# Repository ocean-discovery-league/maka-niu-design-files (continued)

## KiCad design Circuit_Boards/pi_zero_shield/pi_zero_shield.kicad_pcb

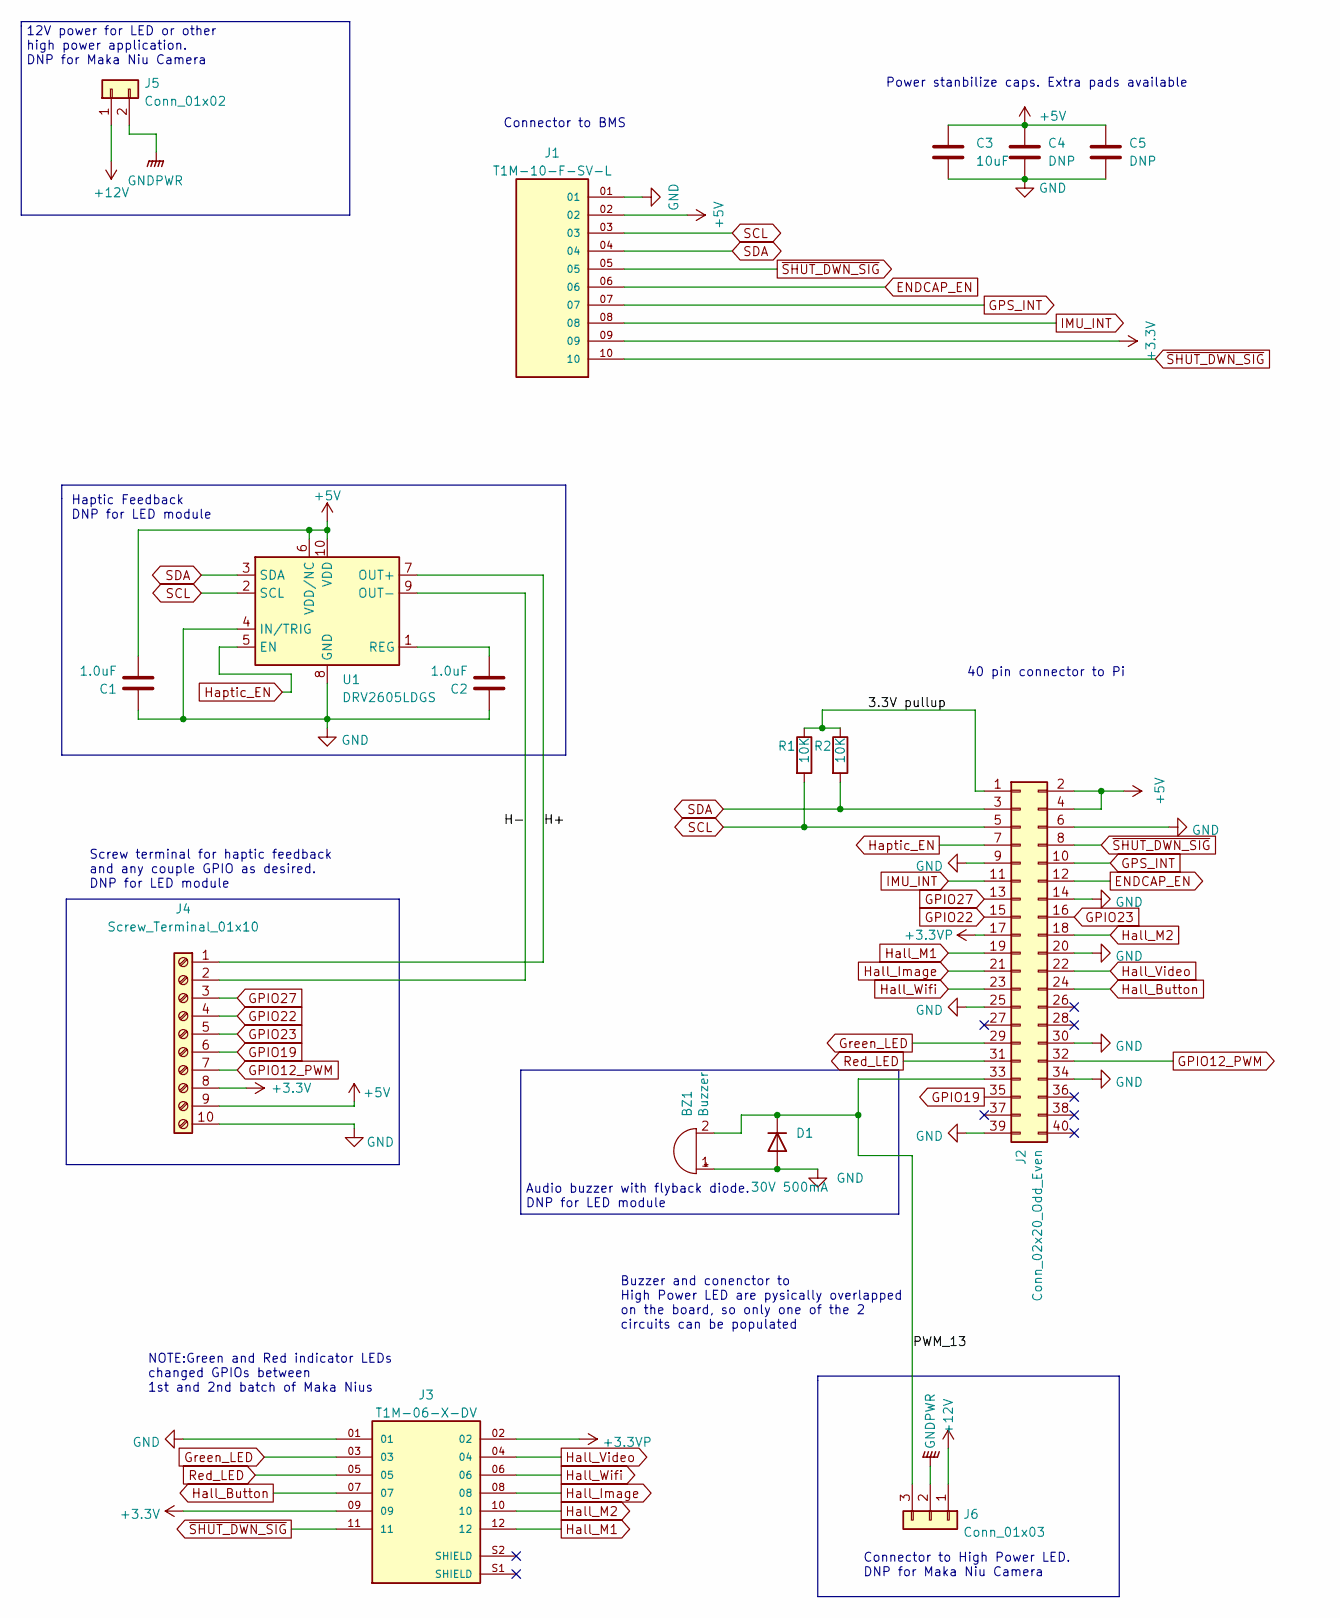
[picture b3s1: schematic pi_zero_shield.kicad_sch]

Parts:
BZ1: Buzzer; Buzzer_12x9.5RM7.6; LCSC C968749
C1, C2: 1.0uF; C_0603_1608Metric; LCSC C90540
C3: 10uF; C_1206_3216Metric_Pad1.33x1.80mm_HandSolder; DigiKey 587-TMK316AB7106ML-TCT-ND
C4, C5: DNP; C_1206_3216Metric_Pad1.33x1.80mm_HandSolder
D1: 30V 500mA; D_SOD-123; DigiKey MBR0530T1GOSCT-ND
J1: T1M-10-F-SV-L; SAMTEC_T1M-10-F-SV-L; Digikey SAM16035-ND
J2: Conn_02x20_Odd_Even; Pi_PinSocket_2x20; Digikey 952-3218-ND
J3: T1M-06-X-DV; SAMTEC_T1M-06-X-DV; Digikey -Get from Samtec
J4: Screw_Terminal_01x10; PinHeader_1x10_P2.54mm_Vertical; Digikey ED10567-ND
J5: Conn_01x02; Molex_Micro-Fit_3.0_43650-0210_1x02-1MP_P3.00mm_Horizontal; Digikey WM6264CT-ND
J6: Conn_01x03; Molex_Micro-Fit_3.0_43650-0310_1x03-1MP_P3.00mm_Horizontal; Digikey WM1886CT-ND
R1, R2: 10K; R_0603_1608Metric; LCSC C25804
U1: DRV2605LDGS; VSSOP-10_3x3mm_P0.5mm; LCSC C527464

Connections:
+3.3VP: J2.17, J3.02
+3V3: J1.09, J3.09, J4.8
+5V: C1.1, C3.1, C4.1, C5.1, J1.02, J2.2, J2.4, J4.9, U1.6 (VDD/NC), U1.10 (VDD)
+12V: J5.1, J6.1
/3.3V pullup: J2.1, R1.1, R2.1
/H+: J4.1, U1.7 (OUT+)
/H-: J4.2, U1.9 (OUT-)
/PWM_13: BZ1.2 (+), D1.1 (K), J2.33, J6.3
ENDCAP_EN: J1.06, J2.12
GND: BZ1.1 (-), C1.2, C2.2, C3.2, C4.2, C5.2, D1.2 (A), J1.01, J2.6, J2.9, J2.14, J2.20, J2.25, J2.30, J2.34, J2.39, J3.01, J4.10, U1.4 (IN/TRIG), U1.8 (GND)
GNDPWR: J5.2, J6.2
GPIO12_PWM: J2.32, J4.7
GPIO19: J2.35, J4.6
GPIO22: J2.15, J4.4
GPIO23: J2.16, J4.5
GPIO27: J2.13, J4.3
GPS_INT: J1.07, J2.10
Green_LED: J2.29, J3.03
Hall_Button: J2.24, J3.07
Hall_Image: J2.21, J3.08
Hall_M1: J2.19, J3.12
Hall_M2: J2.18, J3.10
Hall_Video: J2.22, J3.04
Hall_Wifi: J2.23, J3.06
Haptic_EN: J2.7, U1.5 (EN)
IMU_INT: J1.08, J2.11
unnamed: C2.1, U1.1 (REG)
Red_LED: J2.31, J3.05
SCL: J1.03, J2.5, R1.2, U1.2 (SCL)
SDA: J1.04, J2.3, R2.2, U1.3 (SDA)
~SHUT_DWN_SIG: J1.05, J1.10, J2.8, J3.11

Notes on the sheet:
Connector to High Power LED. DNP for Maka Niu Camera
Connector to BMS
Buzzer and conenctor to High Power LED are pysically overlapped on the board, so only one of the 2 circuits can be populated
NOTE:Green and Red indicator LEDs changed GPIOs between 1st and 2nd batch of Maka Nius
12V power for LED or other high power application. DNP for Maka Niu Camera
Haptic Feedback DNP for LED module
Power stanbilize caps. Extra pads available
Screw terminal for haptic feedback and any couple GPIO as desired. DNP for LED module
40 pin connector to Pi
Audio buzzer with flyback diode. DNP for LED module

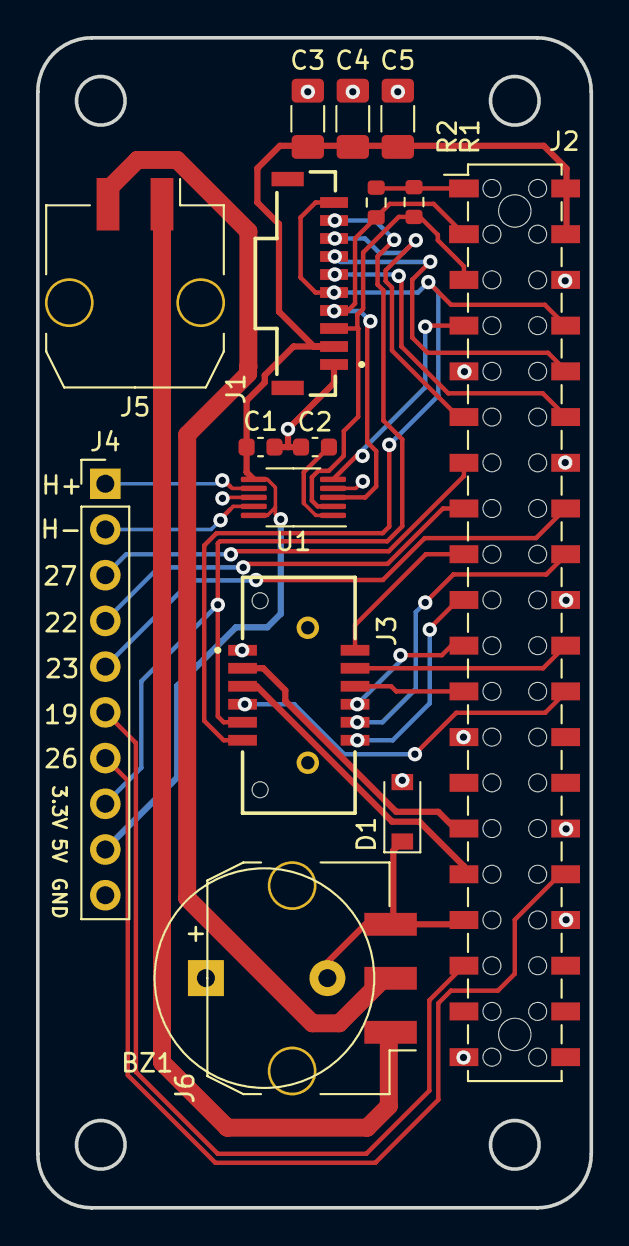
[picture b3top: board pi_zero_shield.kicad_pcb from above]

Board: 2 copper layers, 30.8 x 65.0 mm, 16 parts (0 on the bottom side), 31 nets.

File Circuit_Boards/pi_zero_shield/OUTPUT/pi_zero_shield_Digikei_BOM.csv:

Reference, Quantity, Value, Buy Digikey, Digikey, LCSC, Mouser
BZ1 ,1,Buzzer,skip,668-1466-ND,C968749,
C1 C2 ,2,1.0uF,skip,1276-1102-1-ND,C90540,
J1 ,1,T1M-10-F-SV-L,skip: SAMTEC,SAM16035-ND,,
J2 ,1,Conn_02x20_Odd_Even,Buy,952-3218-ND,,
J3 ,1,T1M-06-X-DV,skip: SAMTEC,,,
J4 ,1,Screw_Terminal_01x10,Buy,ED10567-ND,,
J5 ,1,Conn_01x02,Buy,WM6264CT-ND,,
J6 ,1,Conn_01x03,Buy,WM1886CT-ND,,
R1 R2 ,2,10K,skip,RNCP0603FTD10K0CT-ND,C25804,
U1 ,1,DRV2605LDGS,Buy: Mouser,296-40032-1-ND,C527464,595-DRV2605LDGSR
Motor,1,,Buy,1670-VC1234B016F-ND,,

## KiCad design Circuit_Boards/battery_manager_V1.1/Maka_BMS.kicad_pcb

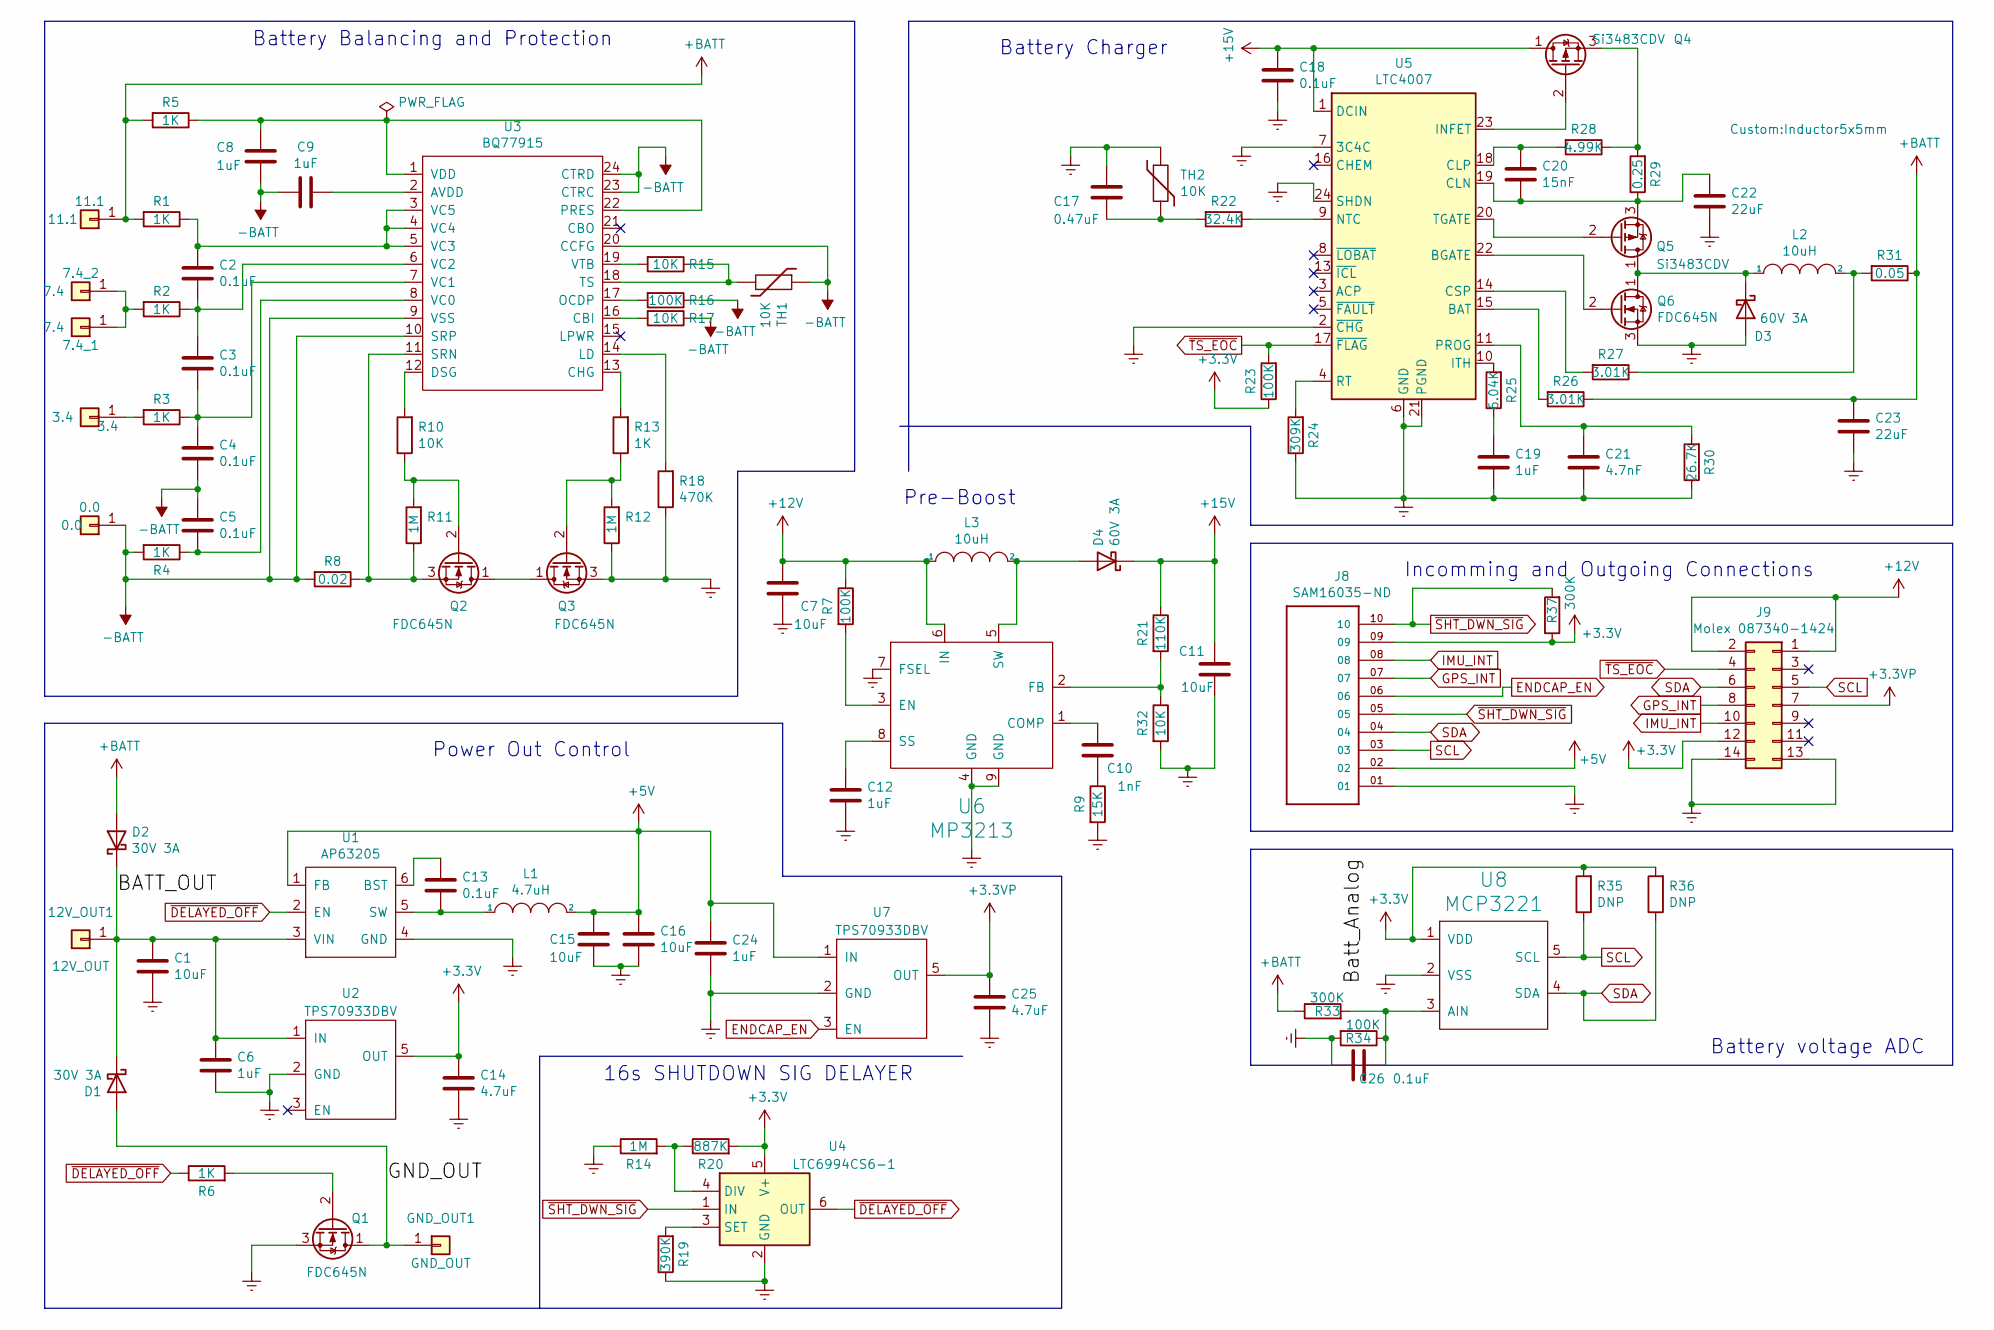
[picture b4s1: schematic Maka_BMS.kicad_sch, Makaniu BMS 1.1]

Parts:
0.0: 0.0; TruHole_Batter_Contact_Pad_with_9mm_clear; Digikey 36-240-ND
3.4: 3.4; TestPoint_THTPad_D1.5mm_Drill0.7mm
7.4_1, 7.4_2: 7.4; TruHole_Batter_Contact_Pad_with_9mm_clear; Digikey 36-240-ND
11.1: 11.1; TestPoint_THTPad_D1.5mm_Drill0.7mm
12V_OUT1: 12V_OUT; TestPoint_THTPad_D1.5mm_Drill0.7mm
C1, C7, C11, C15, C16: 10uF; C_0603_1608Metric; Digikey 490-7202-1-ND
C2, C3, C4, C5, C13, C18, C26: 0.1uF; C_0402_1005Metric; Digikey 732-7495-1-ND
C6, C8, C9, C12, C19, C24: 1uF; C_0402_1005Metric; Digikey 490-10017-1-ND
C10: 1nF; C_0402_1005Metric; Digikey 478-1101-2-ND
C14, C25: 4.7uF; C_0603_1608Metric; Digikey 1276-1900-1-ND
C17: 0.47uF; C_0402_1005Metric; Digikey 490-12269-1-ND
C20: 15nF; C_0402_1005Metric; Digikey 311-1713-1-ND
C21: 4.7nF; C_0402_1005Metric; Digikey 311-1039-1-ND
C22, C23: 22uF; C_0603_1608Metric; Digikey 1276-7076-1-ND
D1, D2: 30V 3A; SMA(DO-214AC); Digikey B340A-FDICT-ND
D3, D4: 60V 3A; D_SOD-123EP; Digikey SSA36CT-ND
GND_OUT1: GND_OUT; TestPoint_THTPad_D1.5mm_Drill0.7mm
J8: ‎SAM16035-ND‎; SAMTEC_T1M-10-F-SH-L-K; Digikey SAM11993-ND
J9: Molex 087340-1424; Molex_87340-1424_B; Digikey 23-0873401424-ND
L1: 4.7uH; L_1008_2520Metric; Digikey 490-10651-1-ND
L2, L3: 10uH; Inductor5x5mm; Digikey 1589-MPL-SE6040-100CT-ND
Q1, Q2, Q3, Q6: FDC645N; SOT-23-6_mosfet; Digikey FDC655BNCT-ND
Q4, Q5: Si3483CDV; SOT-23-6_mosfet; Digikey CPH6350-TL-WOSCT-ND
R1, R2, R3, R4, R5, R6, R13: 1K; R_0402_1005Metric; Digikey YAG1234CT-ND
R7, R16, R23, R34: 100K; R_0402_1005Metric; Digikey 311-100KLRCT-ND
R8: 0.02; R_1206_3216Metric; Digikey WSLP-.02CT-ND
R9: 15K; R_0402_1005Metric; Digikey 311-15.0KLRTR-ND
R10, R15, R17, R32: 10K; R_0402_1005Metric; Digikey 311-10.0KLRCT-ND
R11, R12, R14: 1M; R_0402_1005Metric; Digikey 311-1.00MLRCT-ND
R18: 470K; R_0402_1005Metric; Digikey 311-470KJRCT-ND
R19: 390K; R_0402_1005Metric; Digikey YAG3143CT-ND
R20: 887K; R_0402_1005Metric; Digikey YAG5696CT-ND
R21: 110K; R_0402_1005Metric; Digikey 311-110KLRCT-ND
R22: 32.4K; R_0402_1005Metric; Digikey YAG3119CT-ND
R24: 309K; R_0402_1005Metric; Digikey YAG3108CT-ND
R25: 6.04K; R_0402_1005Metric; Digikey YAG2293CT-ND
R26, R27: 3.01K; R_0402_1005Metric; Digikey 311-3.01KLRCT-ND
R28: 4.99K; R_0402_1005Metric; Digikey YAG1447CT-ND
R29: 0.25; R_1206_3216Metric; Digikey 311-0.25ANCT-ND
R30: 26.7K; R_0402_1005Metric; Digikey YAG3081CT-ND
R31: 0.05; R_1206_3216Metric; Digikey MCS1632R050FERCT-ND
R33, R37: 300K; R_0402_1005Metric; Digikey 311-300KLRCT-ND
R35, R36: DNP; R_0402_1005Metric
TH1: 10K; R_0402_1005Metric; Digikey 495-5814-1-ND
TH2: 10K; R_0402_1005Metric; Digikey 311-10.0KLRCT-ND
U1: AP63205; TSOT-23-6; Digikey AP63205WU-7DICT-ND
U2, U7: TPS70933DBV; SOT-23-5; Digikey 497-6979-1-ND
U3: BQ77915; TSSOP-24_4.4x7.8mm_P0.65mm; Digikey 296-50995-1-ND
U4: LTC6994CS6-1; TSOT-23-6; Digikey LTC6994CS6-1#TRMPBFCT-ND
U5: LTC4007; SSOP-24_3.9x8.7mm_P0.635mm; Digikey LTC4007EGN#PBF-ND
U6: MP3213; MSOP-8-1EP_3x3mm_P0.65mm_EP1.95x2.15mm; Digikey 1589-1626-1-ND
U8: MCP3221; SOT-23-5; LCSC C36310

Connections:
+3.3VP: C25.2, J9.7, U7.5 (OUT)
+3V3: C14.2, J8.09, J9.12, R20.2, R23.1, R35.2, R36.2, R37.1, U2.5 (OUT), U4.5 (V+), U8.1 (VDD)
+5V: C15.2, C16.2, C24.2, J8.02, L1.2, U1.1 (FB), U7.1 (IN)
+12V: C7.1, J9.1, J9.2, L3.1, R7.1, U6.6 (IN)
+15V: C11.1, C18.2, D4.1 (K), Q4.1 (D), R21.1, U5.1 (DCIN)
+BATT: 11.1.1, C23.2, D2.2 (A), R1.2, R5.2, R26.1, R31.1, R33.1
-BATT: 0.0.1, C4.1, C5.2, C8.1, C9.2, R4.2, R8.2, R16.1, R17.1, TH1.1, U3.9 (VSS), U3.10 (SRP), U3.20 (CCFG), U3.23 (CTRC), U3.24 (CTRD)
/BATT_OUT: 12V_OUT1.1, C1.2, C6.2, D1.1 (K), D2.1 (K), U1.3 (VIN), U2.1 (IN)
/GND_OUT: D1.2 (A), GND_OUT1.1, Q1.1 (D)
ENDCAP_EN: J8.06, U7.3 (EN)
Earth: C1.1, C6.1, C7.2, C11.2, C12.1, C14.1, C15.1, C16.1, C17.2, C18.1, C19.1, C21.1, C22.1, C23.1, C24.1, C25.1, C26.2, D3.2 (A), J8.01, J9.13, J9.14, Q1.3 (S), Q3.3 (S), Q6.3 (S), R9.2, R12.1, R14.1, R18.1, R19.1, R24.1, R30.1, R32.2, R34.2, TH2.1, U1.4 (GND), U2.2 (GND), U4.2 (GND), U5.2 (~CHG), U5.6 (GND), U5.7 (3C4C), U5.21 (PGND), U5.24 (SHDN), U6.4 (GND), U6.7 (FSEL), U6.9 (GND), U7.2 (GND), U8.2 (VSS)
GPS_INT: J8.07, J9.8
IMU_INT: J8.08, J9.10
unnamed: 3.4.1, R3.2
unnamed: 7.4_1.1, 7.4_2.1, R2.2
unnamed: C2.1, C3.2, R2.1, U3.6 (VC2)
unnamed: C2.2, R1.1, U3.3 (VC5), U3.4 (VC4), U3.5 (VC3)
unnamed: C3.1, C4.2, R3.1, U3.7 (VC1)
unnamed: C5.1, R4.1, U3.8 (VC0)
unnamed: C8.2, R5.1, U3.1 (VDD), U3.22 (PRES)
unnamed: C9.1, U3.2 (AVDD)
unnamed: C10.1, U6.1 (COMP)
unnamed: C10.2, R9.1
unnamed: C12.2, U6.8 (SS)
unnamed: C13.1, L1.1, U1.5 (SW)
unnamed: C13.2, U1.6 (BST)
unnamed: C17.1, R22.2, TH2.2
unnamed: C19.2, R25.1
unnamed: C20.1, C22.2, Q5.3 (S), R29.1, U5.19 (CLN)
unnamed: C20.2, R28.2, U5.18 (CLP)
unnamed: C21.2, R30.2, U5.11 (PROG)
unnamed: D3.1 (K), L2.1, Q5.1 (D), Q6.1 (D)
unnamed: D4.2 (A), L3.2, U6.5 (SW)
unnamed: L2.2, R27.1, R31.2
unnamed: Q1.2 (G), R6.2
unnamed: Q2.1 (D), Q3.1 (D)
unnamed: Q2.2 (G), R10.1, R11.2
unnamed: Q2.3 (S), R8.1, R11.1, U3.11 (SRN)
unnamed: Q3.2 (G), R12.2, R13.1
unnamed: Q4.2 (G), U5.23 (INFET)
unnamed: Q4.3 (S), R28.1, R29.2
unnamed: Q5.2 (G), U5.20 (TGATE)
unnamed: Q6.2 (G), U5.22 (BGATE)
unnamed: R7.2, U6.3 (EN)
unnamed: R10.2, U3.12 (DSG)
unnamed: R13.2, U3.13 (CHG)
unnamed: R14.2, R20.1, U4.4 (DIV)
unnamed: R15.1, TH1.2, U3.18 (TS)
unnamed: R15.2, U3.19 (VTB)
unnamed: R16.2, U3.17 (OCDP)
unnamed: R17.2, U3.16 (CBI)
unnamed: R18.2, U3.14 (LD)
unnamed: R19.2, U4.3 (SET)
unnamed: R21.2, R32.1, U6.2 (FB)
unnamed: R22.1, U5.9 (NTC)
unnamed: R24.2, U5.4 (RT)
unnamed: R25.2, U5.10 (ITH)
unnamed: R26.2, U5.15 (BAT)
unnamed: R27.2, U5.14 (CSP)
unnamed: C26.1, R33.2, R34.1, U8.3 (AIN)
SCL: J8.03, J9.5, R35.1, U8.5 (SCL)
SDA: J8.04, J9.6, R36.1, U8.4 (SDA)
~DELAYED_OFF: R6.1, U1.2 (EN), U4.6 (OUT)
~SHT_DWN_SIG: J8.05, J8.10, R37.2, U4.1 (IN)
~TS_EOC: J9.4, R23.2, U5.17 (~FLAG)

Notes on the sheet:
Power Out Control
16s SHUTDOWN SIG DELAYER
Battery voltage ADC
Pre-Boost
Battery Charger
Battery Balancing and Protection
Incomming and Outgoing Connections

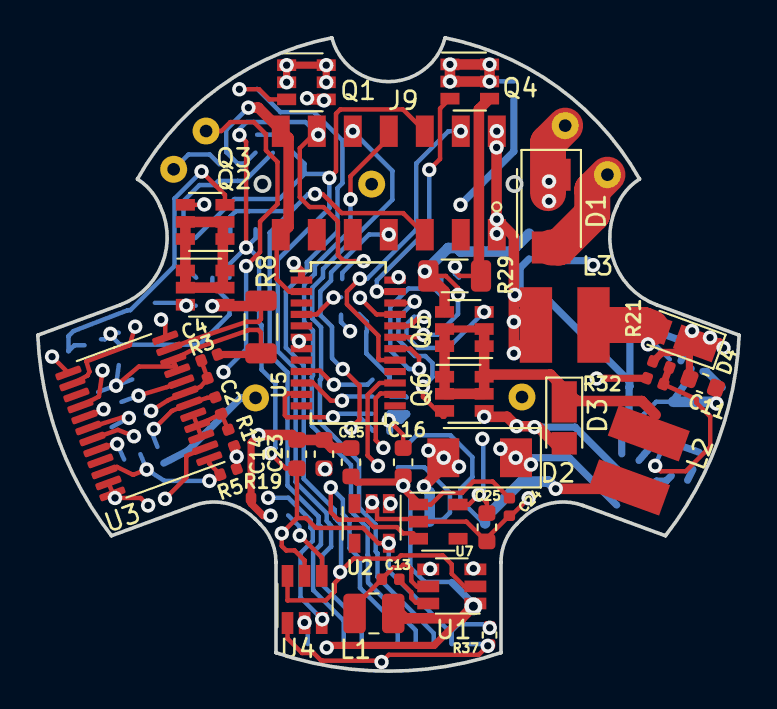
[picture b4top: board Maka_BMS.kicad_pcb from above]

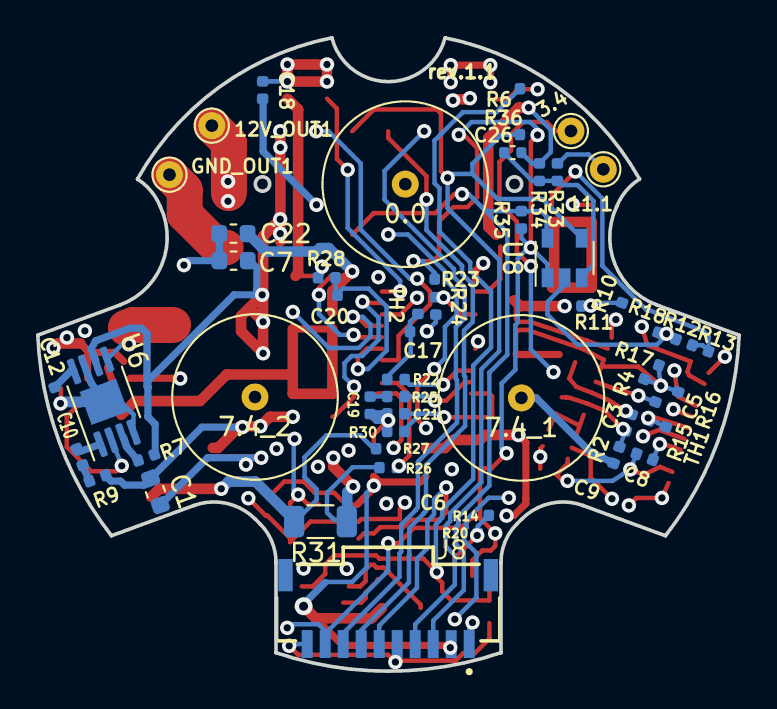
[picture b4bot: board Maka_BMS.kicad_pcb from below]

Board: 4 copper layers, 39.0 x 35.2 mm, 95 parts (56 on the bottom side), 65 nets.

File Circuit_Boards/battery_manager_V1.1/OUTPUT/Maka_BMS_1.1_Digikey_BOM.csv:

Reference, Quantity, Value, Buy Digikey, Digikey, LCSC, Mouser
0,1,0,Buy,36-240-ND,,
7.4_1 7.4_2 ,2,7.4,Buy,36-240-ND,,
C1 C7 C11 C15 C16 ,5,10uF,skip,490-7202-1-ND,C96446,
C10 ,1,1nF,skip,478-1101-2-ND,C1523,
C14 C25 ,2,4.7uF,skip,"	1276-1900-1-ND",C152896,
C17 ,1,0.47uF,skip,490-12269-1-ND,C47339,
C2 C3 C4 C5 C13 C18 ,6,0.1uF,skip,732-7495-1-ND,C155422,
C20 ,1,15nF,skip,"	311-1713-1-ND",C114405,
C21 ,1,4.7nF,skip,"	311-1039-1-ND",C1538,
C22 C23 ,2,22uF,skip,1276-7076-1-ND,C2835567,
C6 C8 C9 C12 C19 C24 ,6,1uF,skip,"	490-10017-1-ND",C52923,
D1 D2 ,2,30V 5A,skip,SK56A-LTPMSTR-ND,C173517,
D3 D4 ,2,60V 3A,skip,SSA36CT-ND,C282393,
J8 ,1, ‎SAM16035-ND‎,skip: SAMTEC,"	SAM11993-ND",,
J9 ,1,Molex 087340-1424,Buy: limited,"	23-0873401424-ND",,
L1 ,1,4.7uH,skip,"	490-10651-1-ND",C391306,
L2 L3 ,2,10uH,skip,1589-MPL-SE6040-100CT-ND,C354610,
Q1 Q2 Q3 Q6 ,4,FDC645N,Buy: Substitute,FDC655BNCT-ND ,C241775,
Q4 Q5 ,2,Si3483CDV,Buy: Substitute,CPH6350-TL-WOSCT-ND,C727455,
R1 R2 R3 R4 R5 R6 R13 ,7,1K,skip,YAG1234CT-ND,C11702,
R10 R15 R17 R32 TH1 TH2 ,6,10K,skip,"	311-10.0KLRCT-ND",C25744,
R11 R12 R14 ,3,1M,skip,311-1.00MLRCT-ND,C26083,
R18 ,1,470K,skip,311-470KJRCT-ND,C25790,
R19 ,1,390K,skip,YAG3143CT-ND,C25782,
R20 ,1,887K,skip,YAG5696CT-ND,C423127,
R21 ,1,110K,skip,311-110KLRCT-ND,C25745,
R22 ,1,32.4K,skip,YAG3119CT-ND,C26974,
R24 ,1,309K,skip,YAG3108CT-ND,C122546,
R25 ,1,6.04K,skip,YAG2293CT-ND,C25913,
R26 R27 ,2,3.01K,skip,"	311-3.01KLRCT-ND",C25889,
R28 ,1,4.99K,skip,YAG1447CT-ND,C25903,
R29 ,1,0.25,skip,311-0.25ANCT-ND,C327073,
R30 ,1,26.7K,skip,"	YAG3081CT-ND",C25876,
R31 ,1,0.05,skip,MCS1632R050FERCT-ND,C127691,
R34 ,1,300K,skip,311-300KLRCT-ND,C25774,
R7 R16 R23 R33 ,4,100K,skip,311-100KLRCT-ND,C25741,
R8 ,1,0.02,skip,WSLP-.02CT-ND,C127690,
R9 ,1,15K,skip,311-15.0KLRTR-ND,C25756,
U1 ,1,AP63205,Buy: No stock,AP63205WU-7DICT-ND,C2071056,
U2 U7 ,2,TPS70933DBV,Buy: substitute,497-6979-1-ND,C89347,
U3 ,1,BQ77915,Buy: No stock,296-50995-1-ND,C2905736,
U4 ,1,LTC6994CS6-1,Buy: No stock,LTC6994CS6-1#TRMPBFCT-ND,C690025,
U5 ,1,LTC4007,Buy: No stock,"	LTC4007EGN#PBF-ND",C687118,
U6 ,1,MP3213,Buy: Mouser,1589-1626-1-ND,,MP3213DH-LF-Z
U8 ,1,MCP3221,Buy,MCP3221A6T-E/OTCT-ND,C36310,
ANT,1,,Buy,478-13411-ND,,
Coil,2,,Buy,732-760308105214-ND,,
Cable 12V,0.5,,Buy,WM25258-ND,,
Cable 5V,1,S1SS-10-28C-GF-06.00-L1,skip:SAMTEC,,,

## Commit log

2022-11-17 added text files with descriptions and links to download design files
2023-01-26 imported all circuit boards from Maka-Niu into Maka-Niu-Design_Files. Additionally, KiCad porject has been cleaned, and small final changes to each design based on experiece from Maka Niu batch 2 hav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
2023-01-26 added instructions for post processing the endcap PCB after receiving from fab house
2023-04-01 cleaned up a bit and mainly added the LED board to the repo
2023-04-05 removed BOM and gerbers for kicad project, to ensure up to date exports
2023-06-26 cosmetic fix to BMS schematic layout
2023-07-21 corrected part number for 10 pin BMS connector
